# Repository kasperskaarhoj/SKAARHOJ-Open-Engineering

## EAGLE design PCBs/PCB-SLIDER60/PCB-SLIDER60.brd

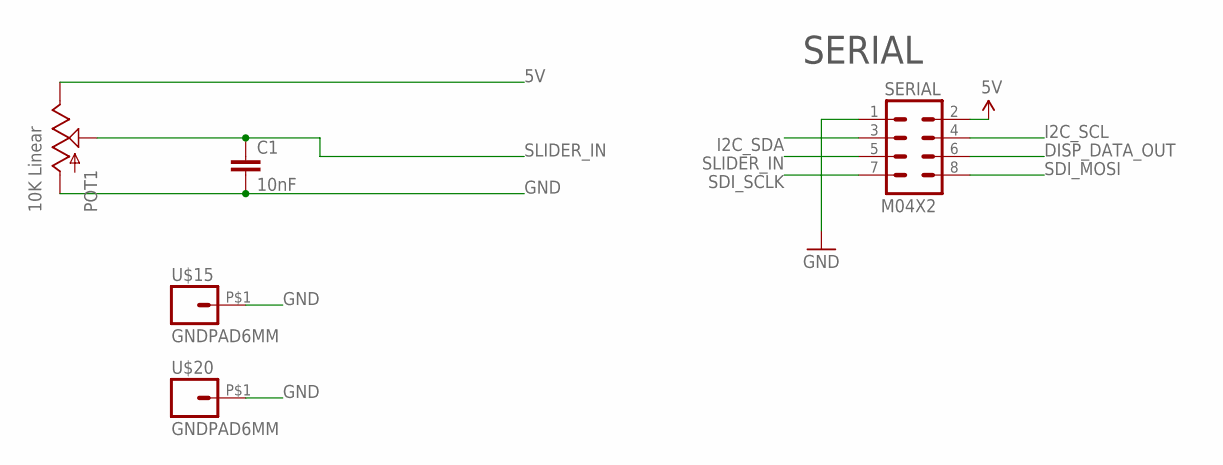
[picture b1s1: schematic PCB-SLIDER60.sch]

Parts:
C1: 10nF; 0603-CAP
POT1: 10K Linear; SLIDER60
SERIAL: M04X2; 2X4
U$15, U$20: GNDPAD6MM; 3.2MMPAD6MM

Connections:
5V: POT1.1 (E), SERIAL.2
DISP_DATA_OUT: SERIAL.6
GND: C1.2, POT1.3 (A), SERIAL.1, U$15.P$1, U$20.P$1
I2C_SCL: SERIAL.4
I2C_SDA: SERIAL.3
SDI_MOSI: SERIAL.8
SDI_SCLK: SERIAL.7
SLIDER_IN: C1.1, POT1.2A (S), SERIAL.5

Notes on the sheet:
SERIAL

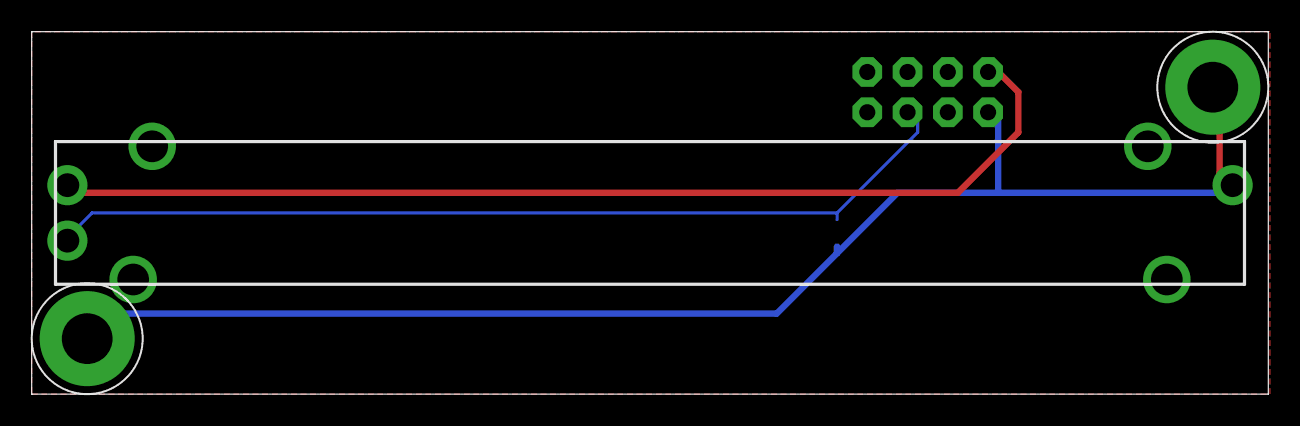
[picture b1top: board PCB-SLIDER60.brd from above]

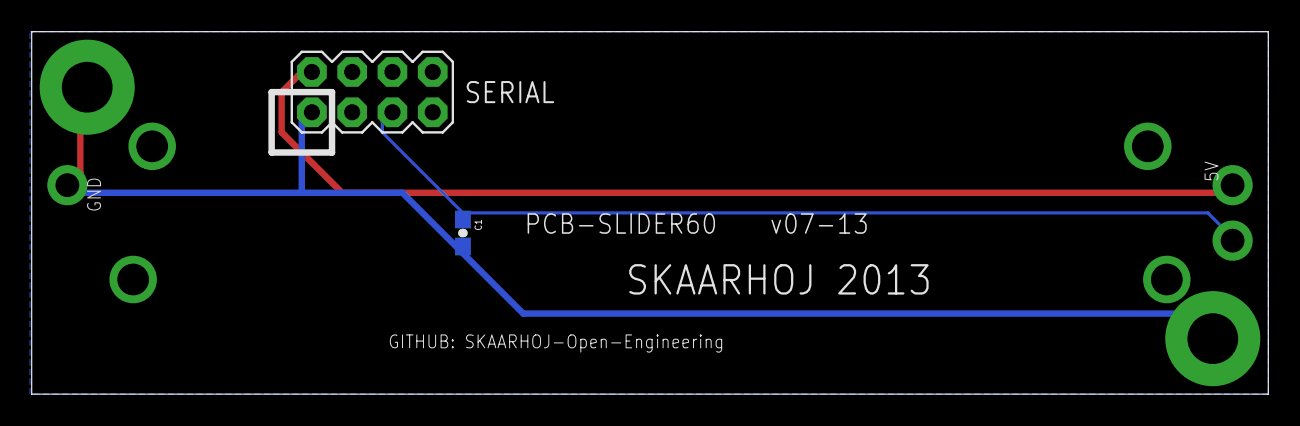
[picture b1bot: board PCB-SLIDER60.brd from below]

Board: 2 copper layers, 78.0 x 22.9 mm, 5 parts (2 on the bottom side), 3 nets.

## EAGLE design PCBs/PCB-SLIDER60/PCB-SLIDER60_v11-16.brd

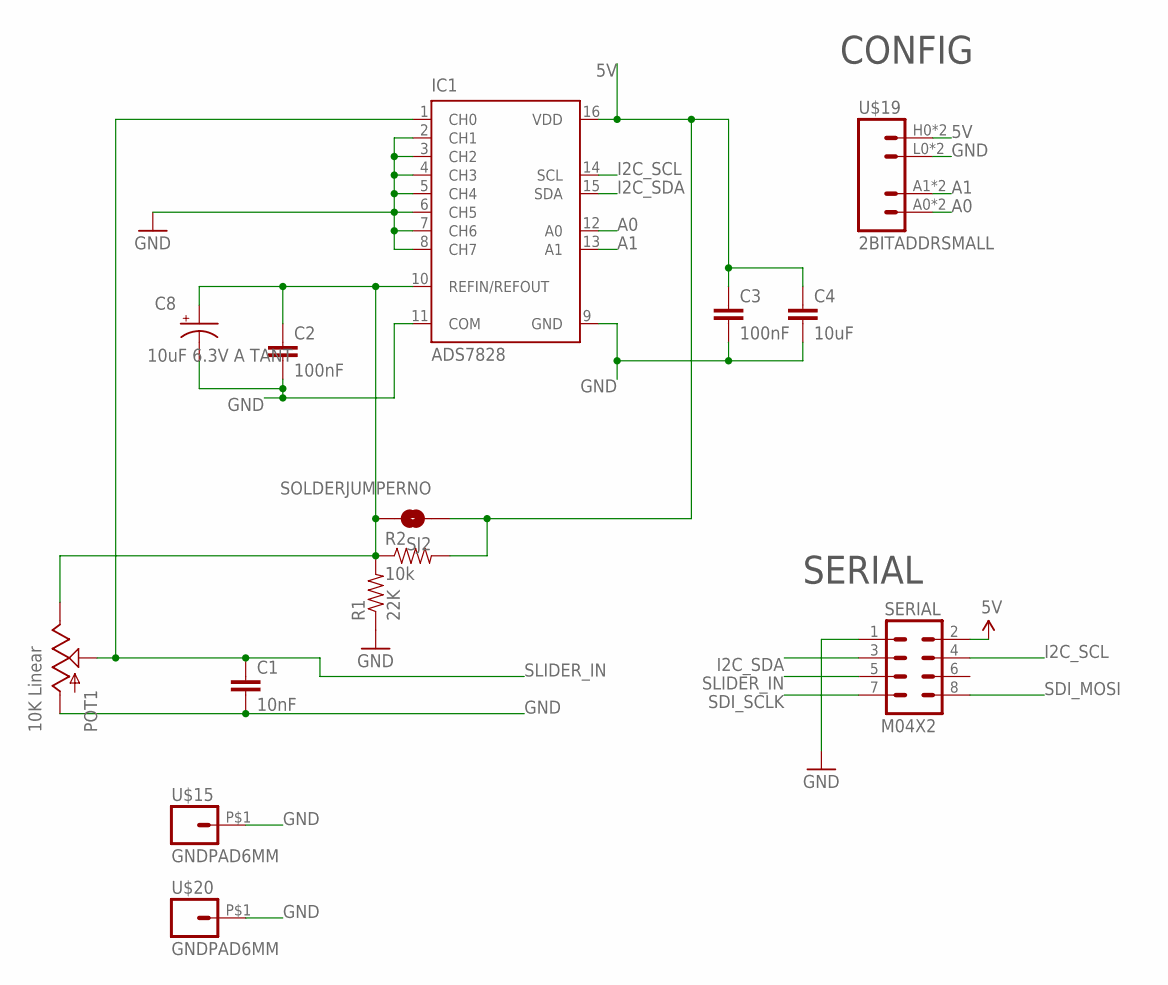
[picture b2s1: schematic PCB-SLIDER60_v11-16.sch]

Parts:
C1: 10nF; 0603-CAP
C2, C3: 100nF; 0603-CAP
C4: 10uF; 0805
C8: 10uF 6.3V A TANT; EIA3216
IC1: ADS7828; TSSOP16-PW
POT1: 10K Linear; SLIDER60
R1: 22K; 0603-RES
R2: 10k; 0603-RES
SERIAL: M04X2; 2X4
SJ2: SOLDERJUMPERNO; SJ_2S-NO
U$15, U$20: GNDPAD6MM; 3.2MMPAD6MM
U$19: 2BITADDRSMALL; 2BITADDR_SMALL

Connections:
5V: C3.1, C4.1, IC1.16 (VDD), R2.2, SERIAL.2, SJ2.1, U$19.H0 (VCC), U$19.H1 (VCC)
A0: IC1.12 (A0), U$19.A0 (A1), U$19.AS0 (A1)
A1: IC1.13 (A1), U$19.A1 (A2), U$19.AS1 (A2)
GND: C1.2, C2.2, C3.2, C4.2, C8.C (-), IC1.2 (CH1), IC1.3 (CH2), IC1.4 (CH3), IC1.5 (CH4), IC1.6 (CH5), IC1.7 (CH6), IC1.8 (CH7), IC1.9 (GND), IC1.11 (COM), POT1.3 (A), R1.1, SERIAL.1, U$15.P$1, U$19.L0 (GND), U$19.L1 (GND), U$20.P$1
I2C_SCL: IC1.14 (SCL), SERIAL.4
I2C_SDA: IC1.15 (SDA), SERIAL.3
unnamed: C2.1, C8.A (+), IC1.10 (REFIN/REFOUT), POT1.1 (E), R1.2, R2.1, SJ2.2
SDI_MOSI: SERIAL.8
SDI_SCLK: SERIAL.7
SLIDER_IN: C1.1, IC1.1 (CH0), POT1.2A (S), SERIAL.5

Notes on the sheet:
SERIAL
CONFIG

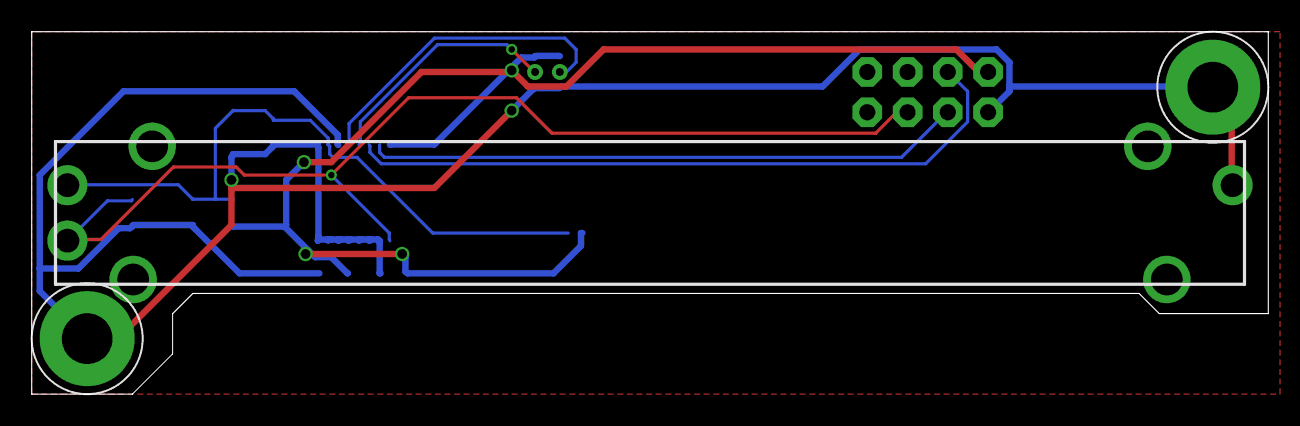
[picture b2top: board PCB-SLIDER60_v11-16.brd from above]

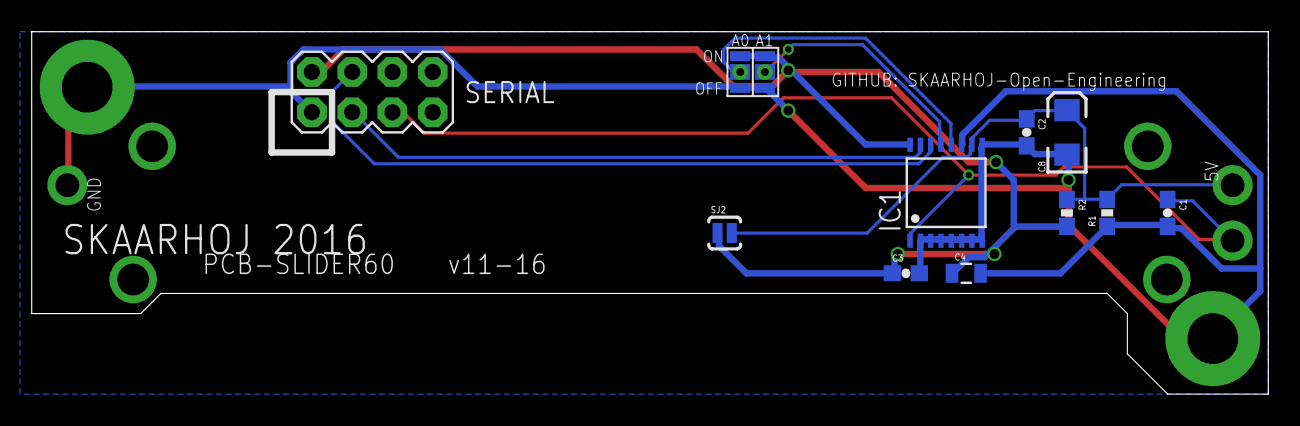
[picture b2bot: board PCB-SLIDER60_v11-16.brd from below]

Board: 2 copper layers, 78.0 x 22.9 mm, 14 parts (11 on the bottom side), 8 nets.

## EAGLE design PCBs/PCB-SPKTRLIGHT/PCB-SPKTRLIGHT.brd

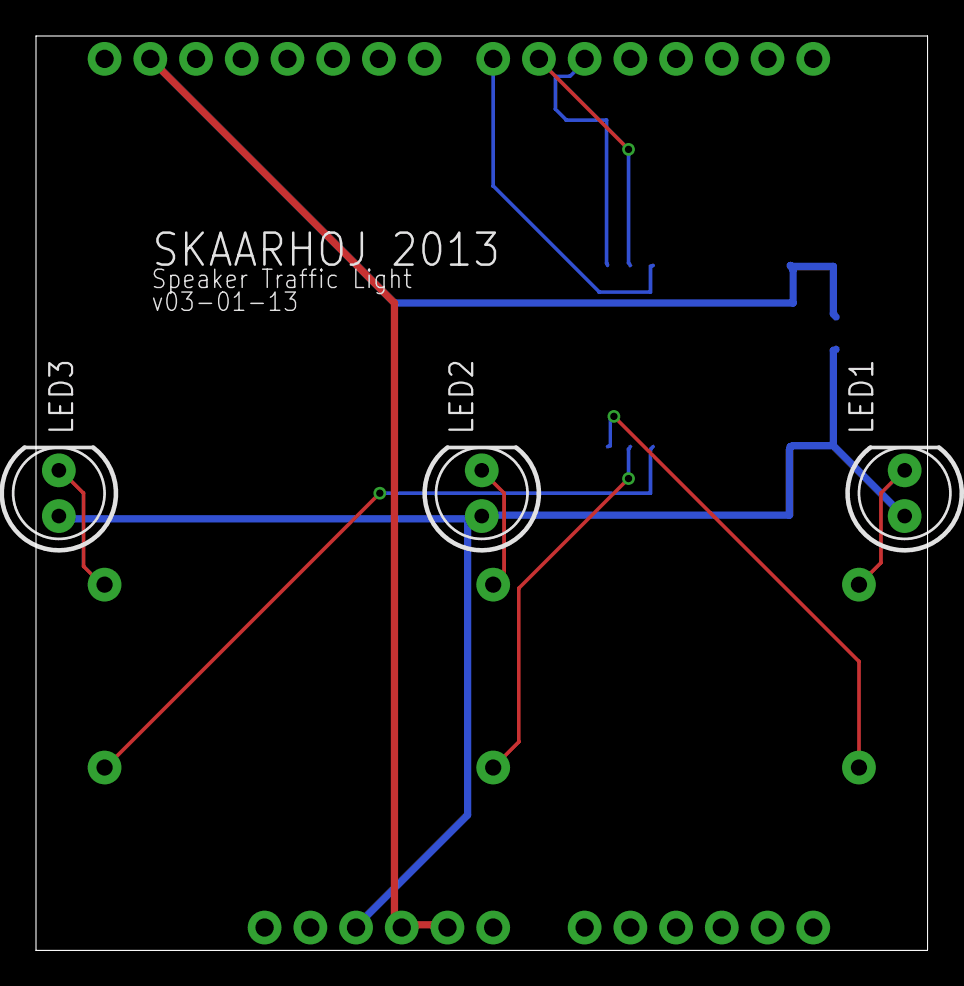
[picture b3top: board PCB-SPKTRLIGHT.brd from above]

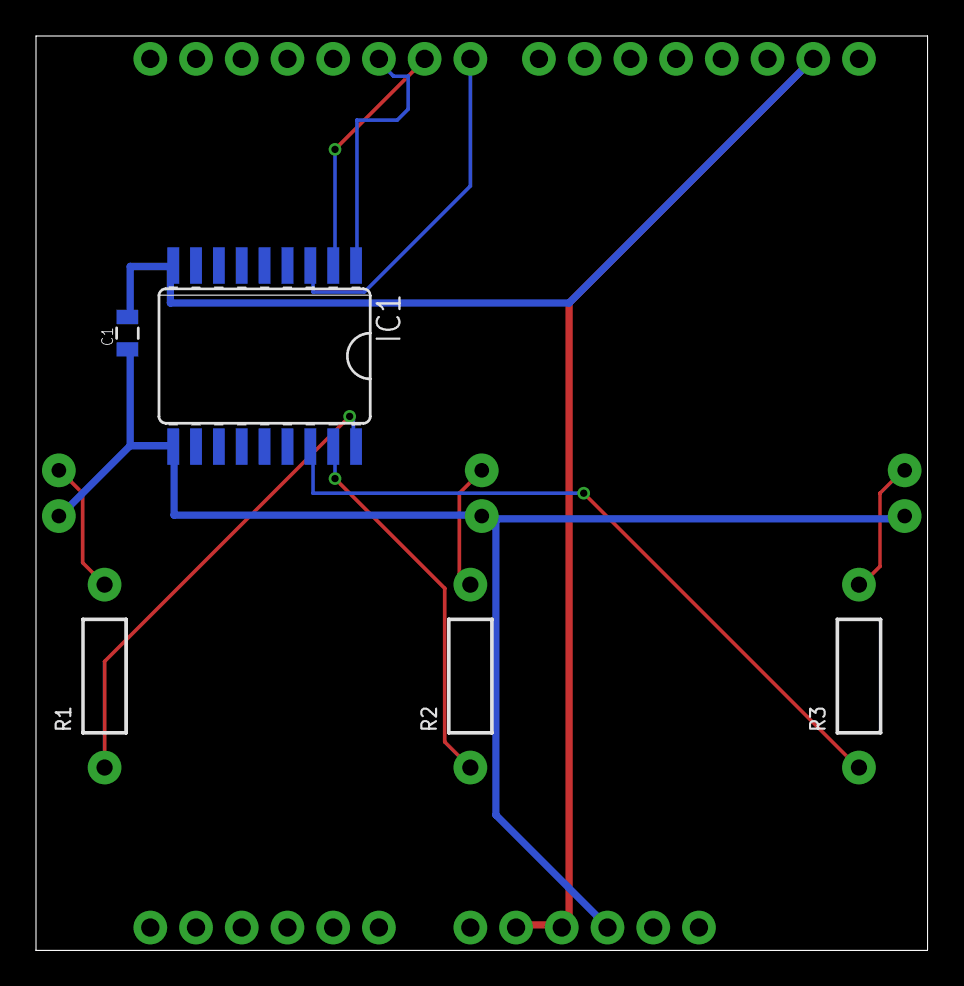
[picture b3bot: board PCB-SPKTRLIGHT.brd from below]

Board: 2 copper layers, 49.5 x 50.8 mm, 9 parts (5 on the bottom side), 11 nets.

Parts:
C1: 100nF; 0805
IC1: ULN2803A; SO18W
LED1: RED; LED5MM
LED2: YELLOW; LED5MM
LED3: GREEN; LED5MM
R1, R2, R3: AXIAL-0.4
U1: ARDUINO_SHIELDNO_SILK; DUEMILANOVE_VIAS

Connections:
5V: C1.1, IC1.10, LED1.A, LED2.A, LED3.A, U1.5V
D5IN: IC1.1, U1.D5
D6IN: IC1.2, U1.D6
D7IN: IC1.3, U1.D7
GND: C1.2, IC1.9, U1.GND@0, U1.GND@1, U1.GND@2
GRNSINK: IC1.16, R3.P$1
unnamed: LED1.K, R1.P$2
unnamed: LED2.K, R2.P$2
unnamed: LED3.K, R3.P$2
REDSINK: IC1.18, R1.P$1
YELSINK: IC1.17, R2.P$1

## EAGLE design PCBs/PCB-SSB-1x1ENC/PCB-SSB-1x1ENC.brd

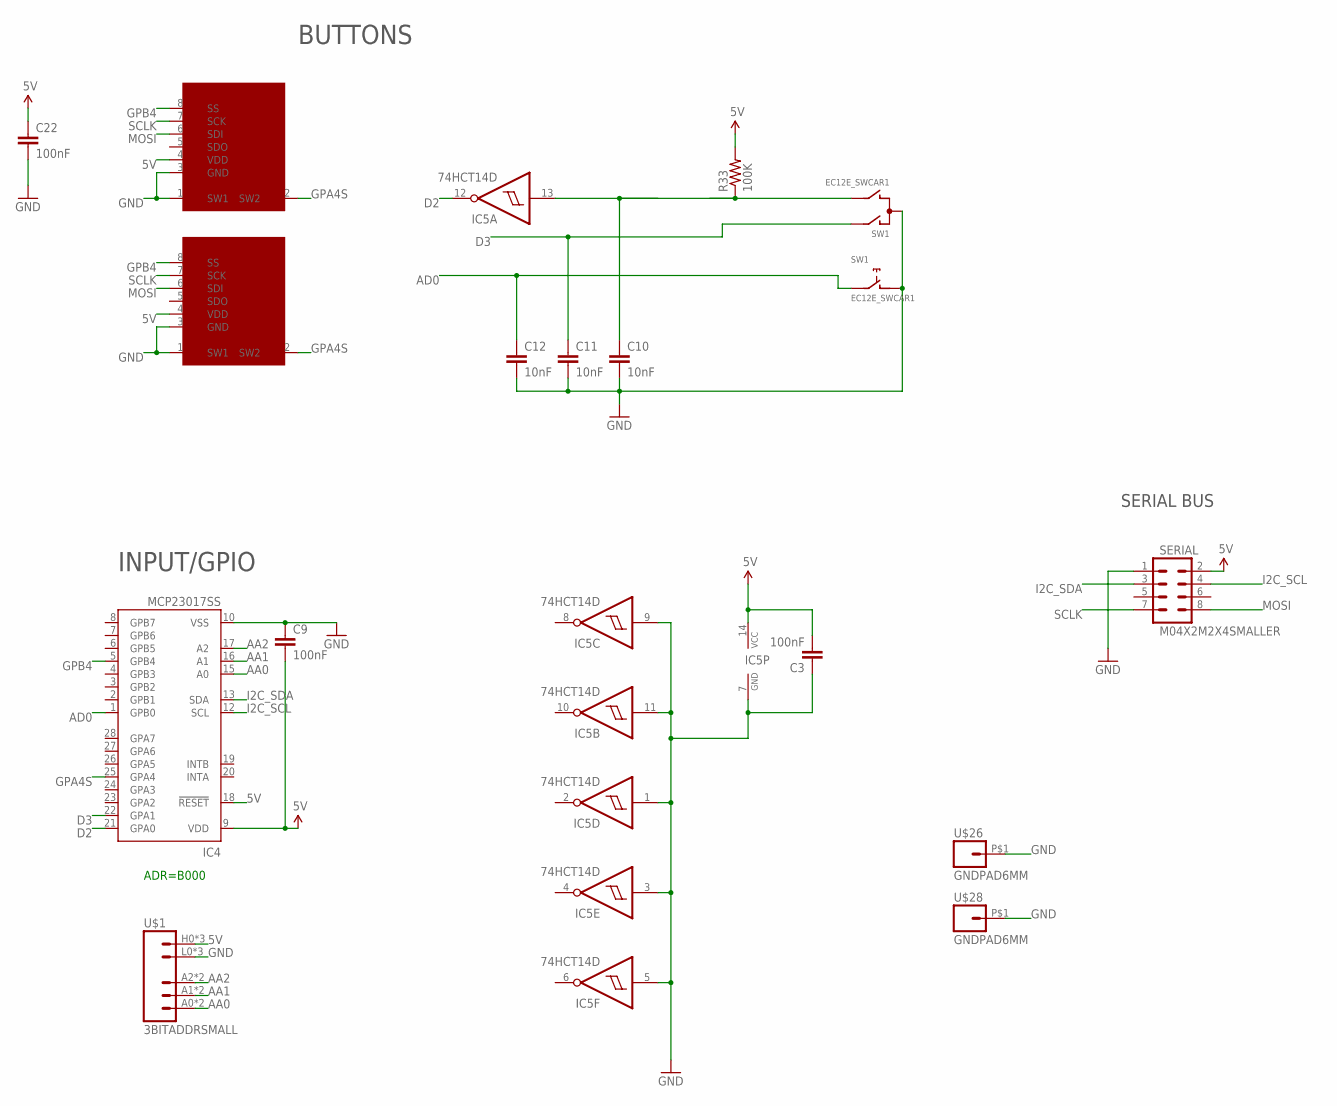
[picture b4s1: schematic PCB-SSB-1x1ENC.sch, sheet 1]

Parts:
C3, C9, C22: 100nF; 0603-CAP
C10, C11, C12: 10nF; 0603-CAP
IC4: MCP23017SS; SSOP28; MPN MCP23017-E/SS
IC5: 74HCT14D; SO14
R33: 100K; 0603-RES
SERIAL: M04X2M2X4SMALLER; M2X4SMALLER
SSW1, SSW1ALT: SMART_SWITCHSMART_SWITCH_8PIN; SMART_SWITCH
SW1: EC12E_SWCAR1; ALPS_EC12E_SW-CAR1
U$1: 3BITADDRSMALL; 3BITADDR_SMALL
U$26, U$28: GNDPAD6MM; 3.2MMPAD6MM

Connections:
5V: C3.2, C9.2, C22.1, IC4.9 (VDD), IC4.18 (!RESET), IC5.14 (VCC), R33.2, SERIAL.2, SSW1.4 (VDD), SSW1ALT.4 (VDD), U$1.H0 (VCC), U$1.H1 (VCC), U$1.H2 (VCC)
AA0: IC4.15 (A0), U$1.A0, U$1.AS0 (A0)
AA1: IC4.16 (A1), U$1.A1, U$1.AS1 (A1)
AA2: IC4.17 (A2), U$1.A2, U$1.AS2 (A2)
AD0: C12.1, IC4.1 (GPB0), SW1.E (2)
D2: IC4.21 (GPA0), IC5.12 (O)
D3: C11.1, IC4.22 (GPA1), SW1.A
GND: C3.1, C9.1, C10.2, C11.2, C12.2, C22.2, IC4.10 (VSS), IC5.1 (I), IC5.3 (I), IC5.5 (I), IC5.7 (GND), IC5.9 (I), IC5.11 (I), SERIAL.1, SSW1.1 (SW1), SSW1.3 (GND), SSW1ALT.1 (SW1), SSW1ALT.3 (GND), SW1.C, SW1.D (1), U$1.L0 (GND), U$1.L1 (GND), U$1.L2 (GND), U$26.P$1, U$28.P$1
GPA4S: IC4.25 (GPA4), SSW1.2 (SW2), SSW1ALT.2 (SW2)
GPB4: IC4.5 (GPB4), SSW1.8 (SS), SSW1ALT.8 (SS)
I2C_SCL: IC4.12 (SCL), SERIAL.4
I2C_SDA: IC4.13 (SDA), SERIAL.3
MOSI: SERIAL.8, SSW1.6 (SDI), SSW1ALT.6 (SDI)
unnamed: C10.1, IC5.13 (I), R33.1, SW1.B
SCLK: SERIAL.7, SSW1.7 (SCK), SSW1ALT.7 (SCK)

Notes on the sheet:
SERIAL BUS
BUTTONS
ADR=B000
INPUT/GPIO

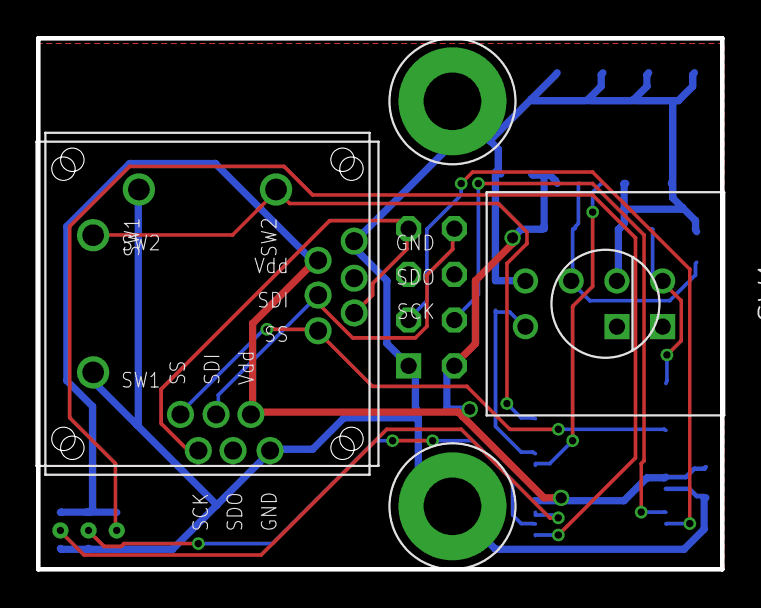
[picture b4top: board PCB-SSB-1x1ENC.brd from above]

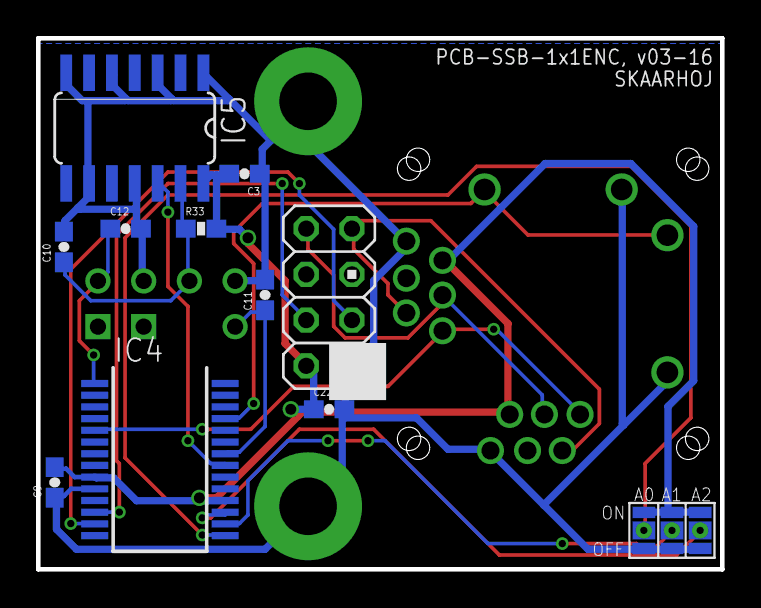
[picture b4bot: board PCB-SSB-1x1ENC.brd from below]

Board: 2 copper layers, 38.0 x 29.5 mm, 16 parts (11 on the bottom side), 15 nets.

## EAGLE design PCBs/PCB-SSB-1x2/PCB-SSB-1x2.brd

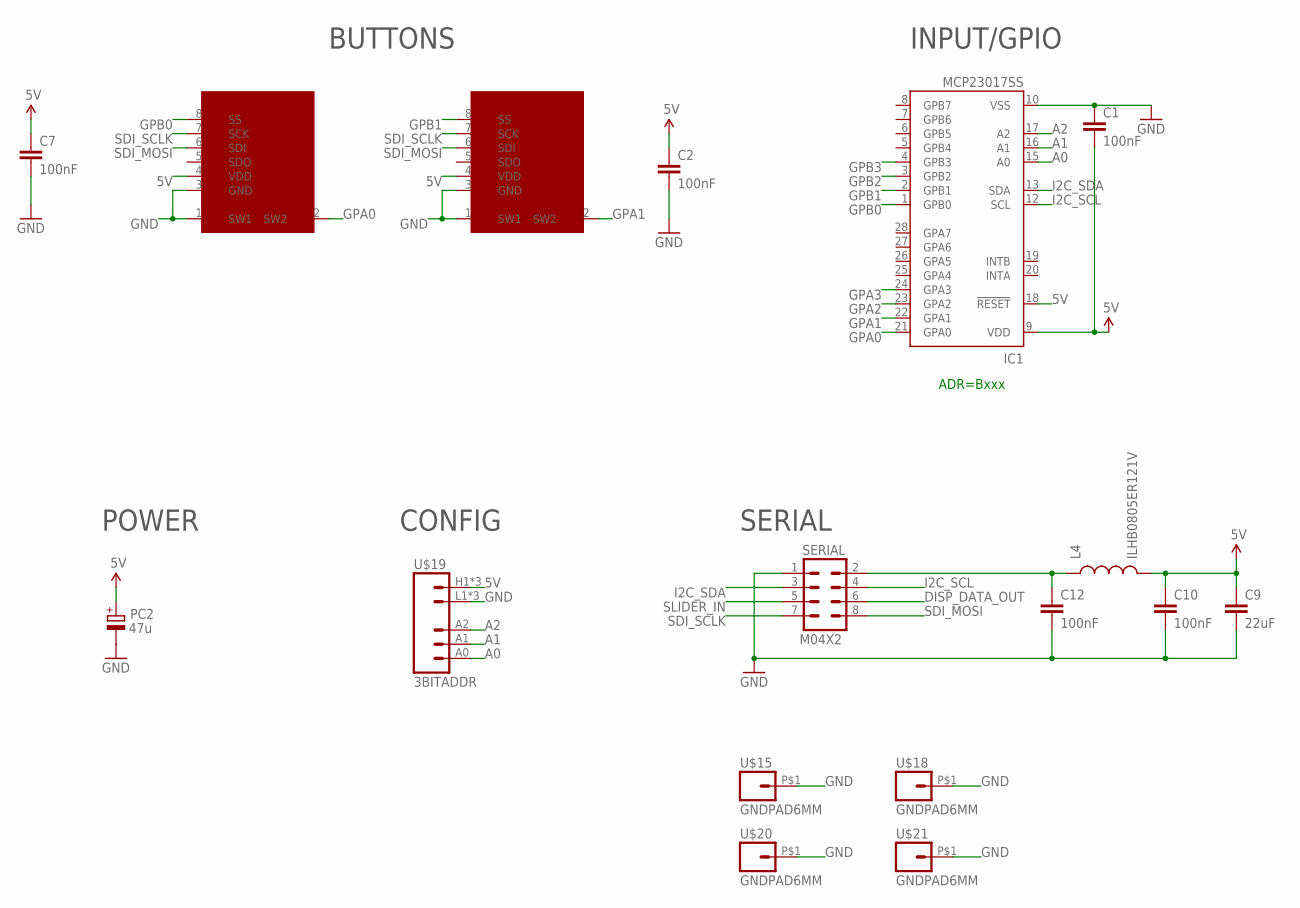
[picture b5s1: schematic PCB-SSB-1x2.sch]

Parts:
C1, C2, C7, C10, C12: 100nF; 0603-CAP
C9: 22uF; 0805
IC1: MCP23017SS; SSOP28; MPN MCP23017-E/SS
L4: ILHB0805ER121V; 0805
PC2: 47u; PANASONIC_D
SERIAL: M04X2; 2X4
SSW1, SSW2: SMART_SWITCHSMART_SWITCH_8PIN; SMART_SWITCH
U$15, U$18, U$20, U$21: GNDPAD6MM; 3.2MMPAD6MM
U$19: 3BITADDR

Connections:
5V: C1.2, C2.1, C7.1, C9.1, C10.1, IC1.9 (VDD), IC1.18 (!RESET), L4.2, PC2.+, SSW1.4 (VDD), SSW2.4 (VDD), U$19.H1 (VCC), U$19.H2 (VCC), U$19.H3 (VCC)
A0: IC1.15 (A0), U$19.A0
A1: IC1.16 (A1), U$19.A1
A2: IC1.17 (A2), U$19.A2
ARD_5V: C12.1, L4.1, SERIAL.2
DISP_DATA_OUT: SERIAL.6
GND: C1.1, C2.2, C7.2, C9.2, C10.2, C12.2, IC1.10 (VSS), PC2.-, SERIAL.1, SSW1.1 (SW1), SSW1.3 (GND), SSW2.1 (SW1), SSW2.3 (GND), U$15.P$1, U$18.P$1, U$19.L1 (GND), U$19.L2 (GND), U$19.L3 (GND), U$20.P$1, U$21.P$1
GPA0: IC1.21 (GPA0), SSW1.2 (SW2)
GPA1: IC1.22 (GPA1), SSW2.2 (SW2)
GPA2: IC1.23 (GPA2)
GPA3: IC1.24 (GPA3)
GPB0: IC1.1 (GPB0), SSW1.8 (SS)
GPB1: IC1.2 (GPB1), SSW2.8 (SS)
GPB2: IC1.3 (GPB2)
GPB3: IC1.4 (GPB3)
I2C_SCL: IC1.12 (SCL), SERIAL.4
I2C_SDA: IC1.13 (SDA), SERIAL.3
SDI_MOSI: SERIAL.8, SSW1.6 (SDI), SSW2.6 (SDI)
SDI_SCLK: SERIAL.7, SSW1.7 (SCK), SSW2.7 (SCK)
SLIDER_IN: SERIAL.5

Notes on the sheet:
ADR=Bxxx
INPUT/GPIO
POWER
SERIAL
BUTTONS
CONFIG

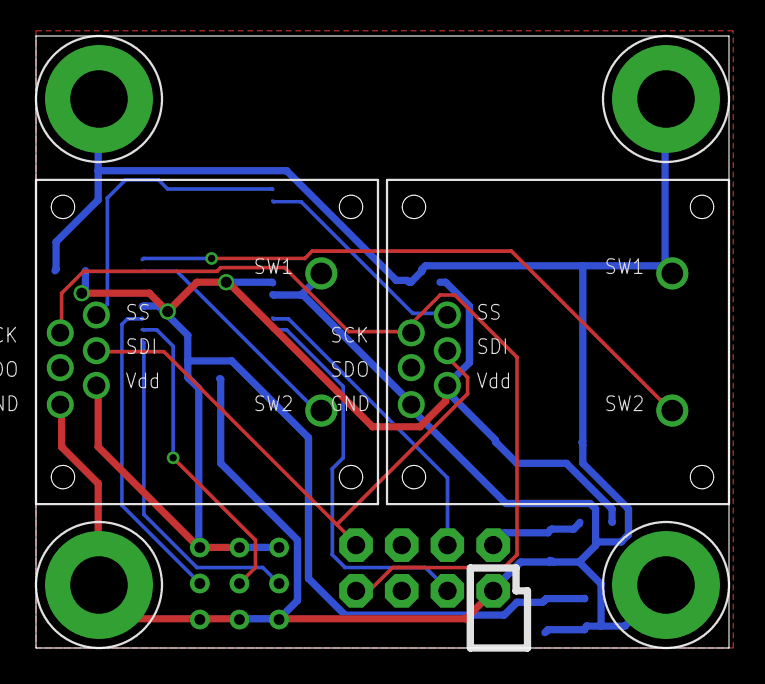
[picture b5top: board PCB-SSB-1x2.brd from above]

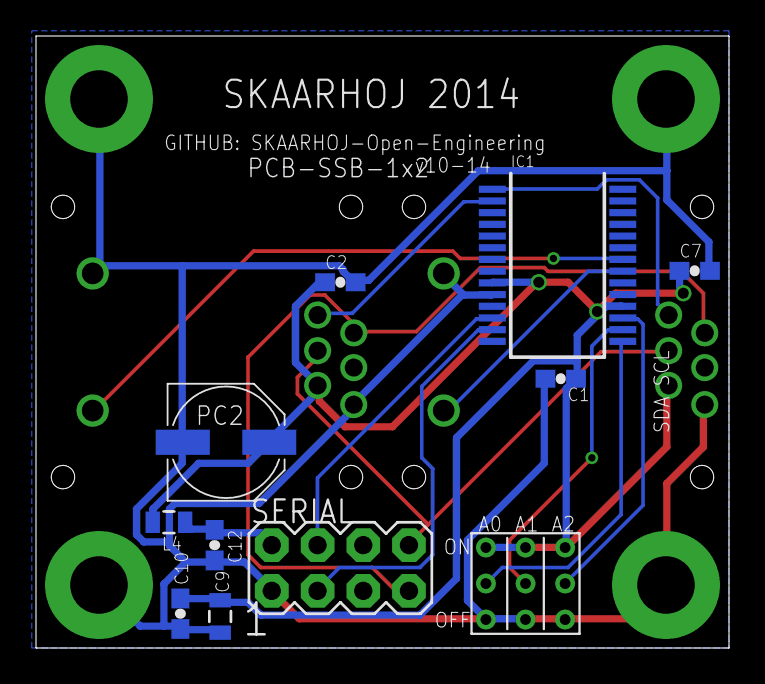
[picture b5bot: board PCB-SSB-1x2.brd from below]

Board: 2 copper layers, 38.5 x 34.0 mm, 17 parts (11 on the bottom side), 14 nets.

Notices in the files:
parts and their libraries:
SparkFun: Licensing: CC v3.0 Share-Alike You are welcome to use this library for commercial purposes.
